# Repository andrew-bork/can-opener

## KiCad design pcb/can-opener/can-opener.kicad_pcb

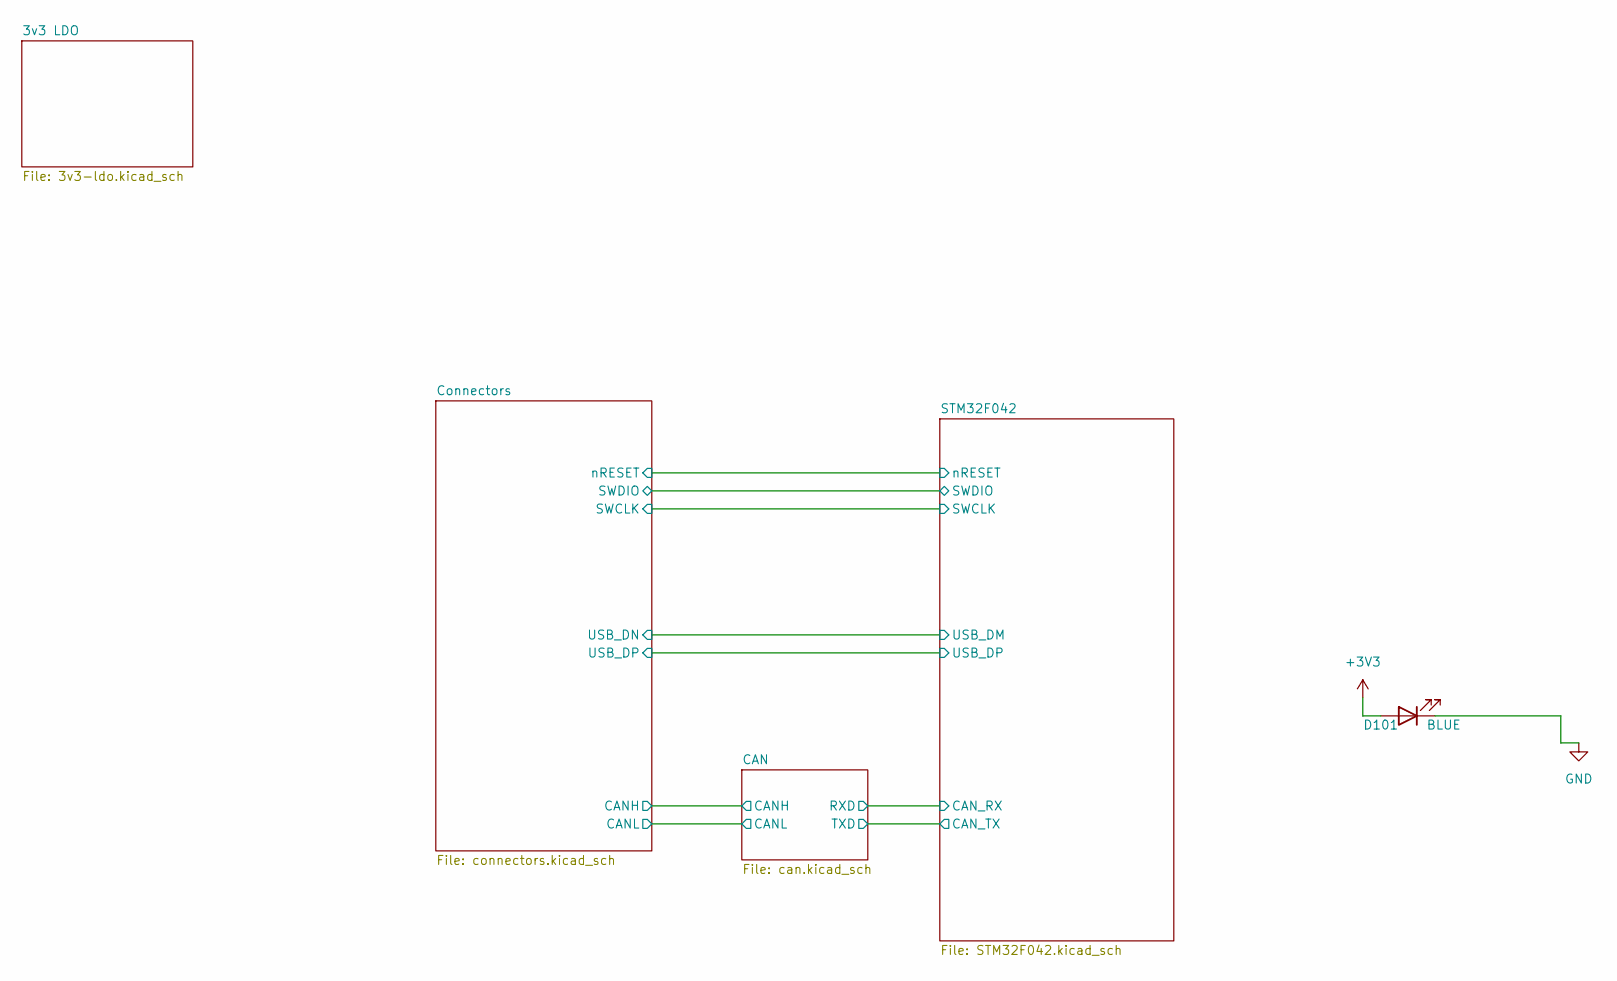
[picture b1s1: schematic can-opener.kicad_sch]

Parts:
D101: BLUE; LED_0603_1608Metric_Pad1.05x0.95mm_HandSolder

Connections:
+3V3: D101.2 (A); also elsewhere on the board
GND: D101.1 (K); also elsewhere on the board

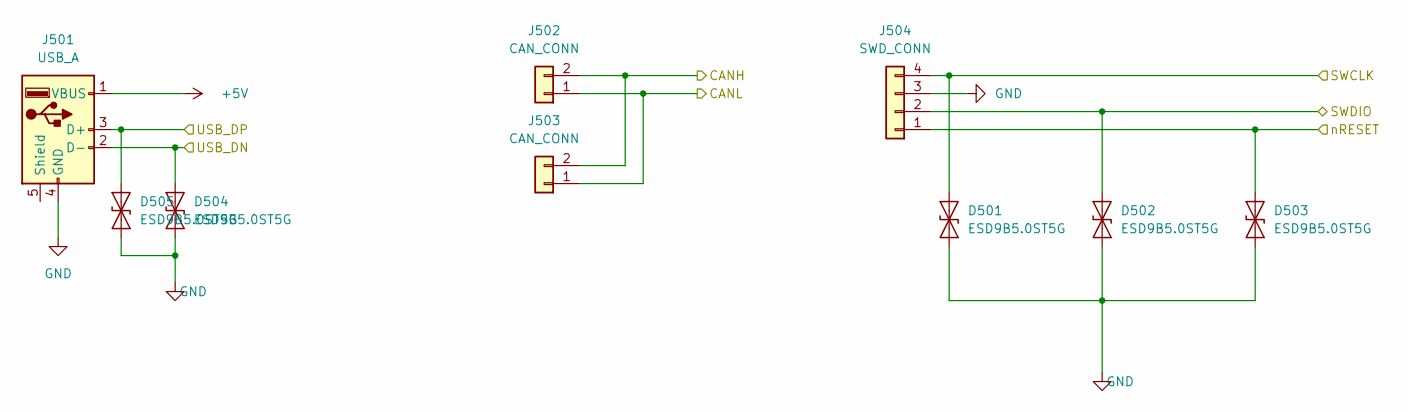
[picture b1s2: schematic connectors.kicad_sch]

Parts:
D501, D502, D503, D504, D505: ESD9B5.0ST5G; D_SOD-923
J501: USB_A; USB_A_Molex_48037-2200_Horizontal
J502, J503: CAN_CONN; JST_XH_S2B-XH-A_1x02_P2.50mm_Horizontal
J504: SWD_CONN; PinHeader_2x02_P2.54mm_Vertical

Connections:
+5V: J501.1 (VBUS); also elsewhere on the board
/CAN/CANH: J502.2, J503.2; also elsewhere on the board
/CAN/CANL: J502.1, J503.1; also elsewhere on the board
/Connectors/SWCLK: D501.2 (A2), J504.4; also elsewhere on the board
/Connectors/SWDIO: D502.2 (A2), J504.2; also elsewhere on the board
/Connectors/USB_DN: D504.2 (A2), J501.2 (D-); also elsewhere on the board
/Connectors/USB_DP: D505.2 (A2), J501.3 (D+); also elsewhere on the board
/Connectors/nRESET: D503.2 (A2), J504.1; also elsewhere on the board
GND: D501.1 (A1), D502.1 (A1), D503.1 (A1), D504.1 (A1), D505.1 (A1), J501.4 (GND), J504.3; also elsewhere on the board

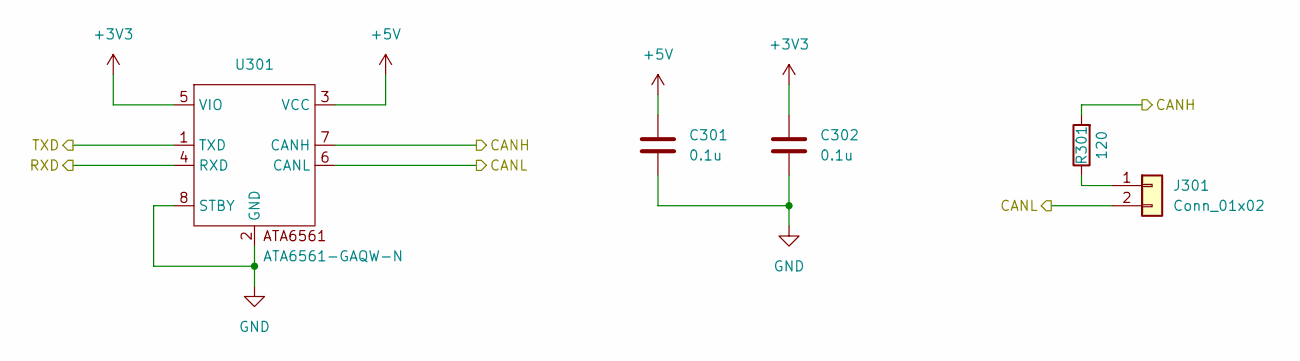
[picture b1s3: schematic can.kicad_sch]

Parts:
C301, C302: 0.1u; C_0402_1005Metric_Pad0.74x0.62mm_HandSolder
J301: Conn_01x02; PinHeader_1x02_P2.54mm_Vertical
R301: 120; R_0402_1005Metric_Pad0.72x0.64mm_HandSolder
U301: ATA6561-GAQW-N; SOIC-8-1EP_3.9x4.9mm_P1.27mm_EP2.41x3.3mm

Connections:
+3V3: C302.1, U301.5 (VIO); also elsewhere on the board
+5V: C301.1, U301.3 (VCC); also elsewhere on the board
/CAN/CANH: R301.2, U301.7 (CANH); also elsewhere on the board
/CAN/CANL: J301.2, U301.6 (CANL); also elsewhere on the board
/CAN/RXD: U301.4 (RXD); also elsewhere on the board
/CAN/TXD: U301.1 (TXD); also elsewhere on the board
GND: C301.2, C302.2, U301.2 (GND), U301.8 (STBY); also elsewhere on the board
unnamed: J301.1, R301.1

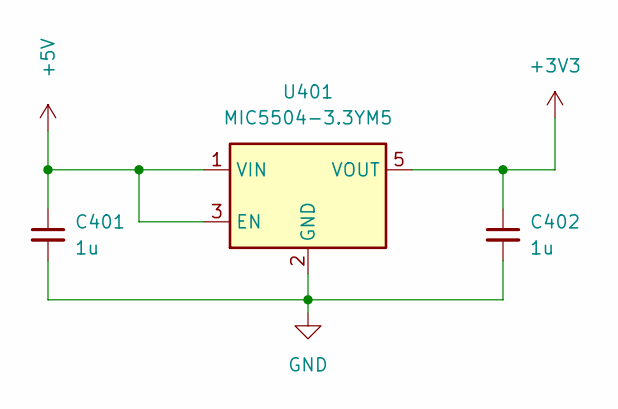
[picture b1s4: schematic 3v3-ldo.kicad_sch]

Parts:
C401, C402: 1u; C_0402_1005Metric_Pad0.74x0.62mm_HandSolder
U401: MIC5504-3.3YM5; SOT-23-5

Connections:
+3V3: C402.1, U401.5 (VOUT); also elsewhere on the board
+5V: C401.1, U401.1 (VIN), U401.3 (EN); also elsewhere on the board
GND: C401.2, C402.2, U401.2 (GND); also elsewhere on the board

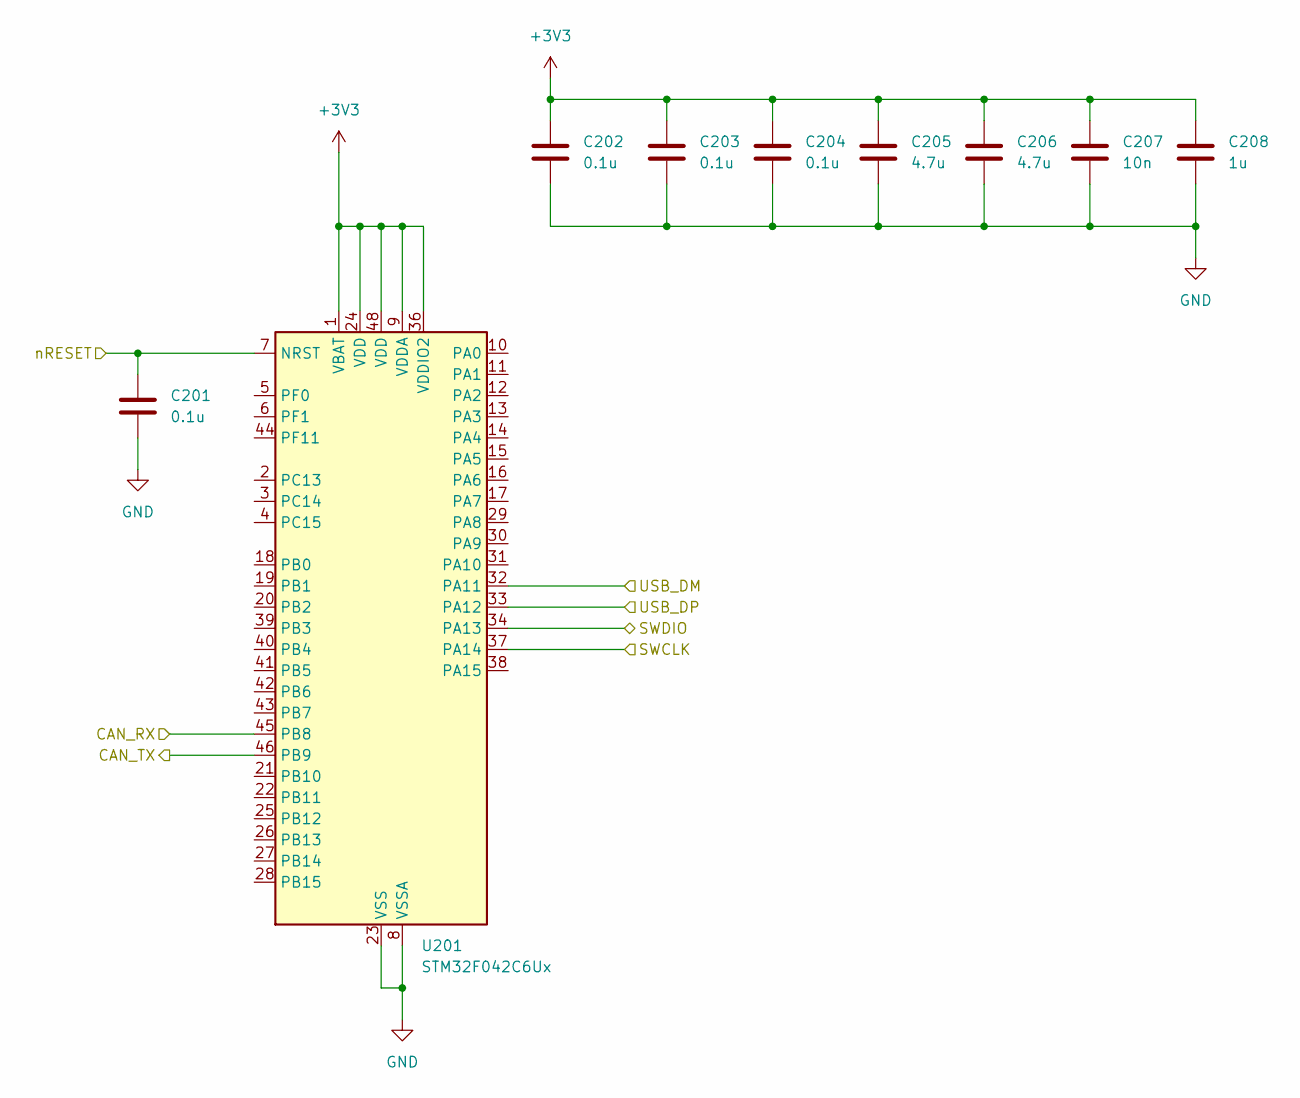
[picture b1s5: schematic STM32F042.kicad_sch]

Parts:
C201, C202, C203, C204: 0.1u; C_0402_1005Metric_Pad0.74x0.62mm_HandSolder
C205, C206: 4.7u; C_0603_1608Metric_Pad1.08x0.95mm_HandSolder
C207: 10n; C_0402_1005Metric_Pad0.74x0.62mm_HandSolder
C208: 1u; C_0402_1005Metric_Pad0.74x0.62mm_HandSolder
U201: STM32F042C6Ux; QFN-48-1EP_7x7mm_P0.5mm_EP5.6x5.6mm

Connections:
+3V3: C202.1, C203.1, C204.1, C205.1, C206.1, C207.1, C208.1, U201.1 (VBAT), U201.9 (VDDA), U201.24 (VDD), U201.36 (VDDIO2), U201.48 (VDD); also elsewhere on the board
/CAN/RXD: U201.45 (PB8); also elsewhere on the board
/CAN/TXD: U201.46 (PB9); also elsewhere on the board
/Connectors/SWCLK: U201.37 (PA14); also elsewhere on the board
/Connectors/SWDIO: U201.34 (PA13); also elsewhere on the board
/Connectors/USB_DN: U201.32 (PA11); also elsewhere on the board
/Connectors/USB_DP: U201.33 (PA12); also elsewhere on the board
/Connectors/nRESET: C201.1, U201.7 (NRST); also elsewhere on the board
GND: C201.2, C202.2, C203.2, C204.2, C205.2, C206.2, C207.2, C208.2, U201.8 (VSSA), U201.23 (VSS), U201.35 (VSS), U201.47 (VSS), U201.49 (VSS); also elsewhere on the board

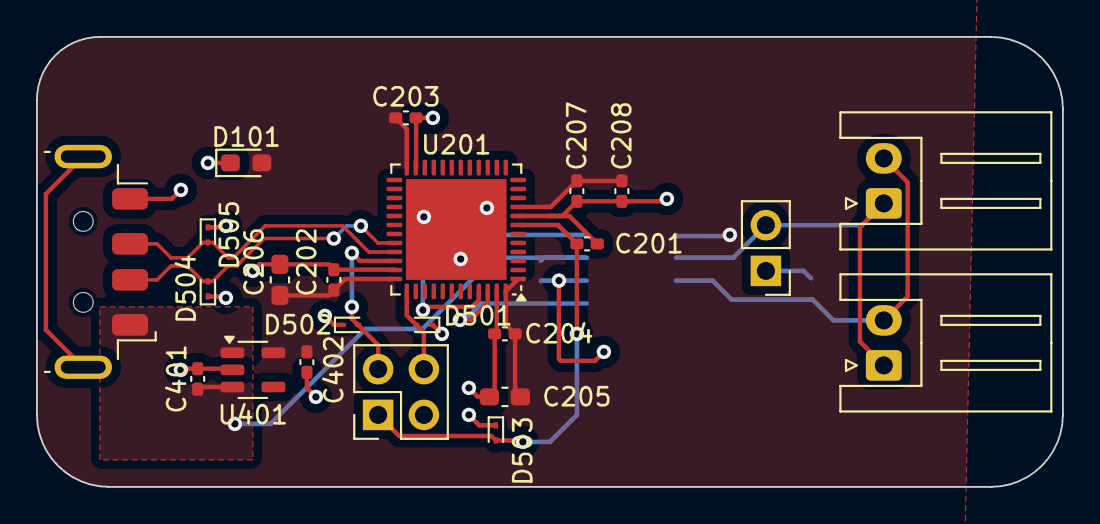
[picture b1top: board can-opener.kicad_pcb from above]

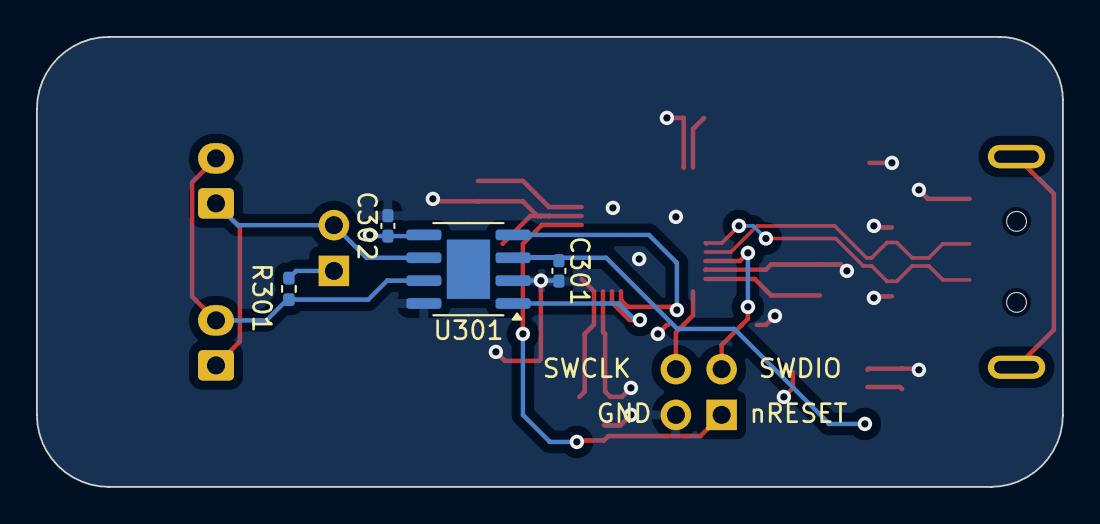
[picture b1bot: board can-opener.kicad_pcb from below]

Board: 2 copper layers, 57.0 x 25.0 mm, 27 parts (4 on the bottom side), 13 nets.

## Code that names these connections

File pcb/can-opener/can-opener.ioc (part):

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Mcu.Name=STM32F042C(4-6)Ux
Mcu.Package=UFQFPN48
Mcu.UserName=STM32F042C6Ux
PA11.Mode=Device
PA11.Signal=USB_DM
PA12.Mode=Device
PA12.Signal=USB_DP
PA13.Mode=Serial_Wire
PA13.Signal=SYS_SWDIO
PA14.Mode=Serial_Wire
PA14.Signal=SYS_SWCLK
PB8.Mode=CAN_Activate
PB8.Signal=CAN_RX
PB9.Mode=CAN_Activate
PB9.Signal=CAN_TX
board=custom

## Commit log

2024-07-09 Finished CAN Opener PCB
